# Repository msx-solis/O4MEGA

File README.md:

# o4Mega v1.
4Mb expansion for OMEGA MSX2+ HOME COMPUTER.
Here is my first board design to expand OMEGA Home Computer from 1Mb to 4Mb of static RAM.
This design is optimized to manufacture the pcb with the toner transfer technique.

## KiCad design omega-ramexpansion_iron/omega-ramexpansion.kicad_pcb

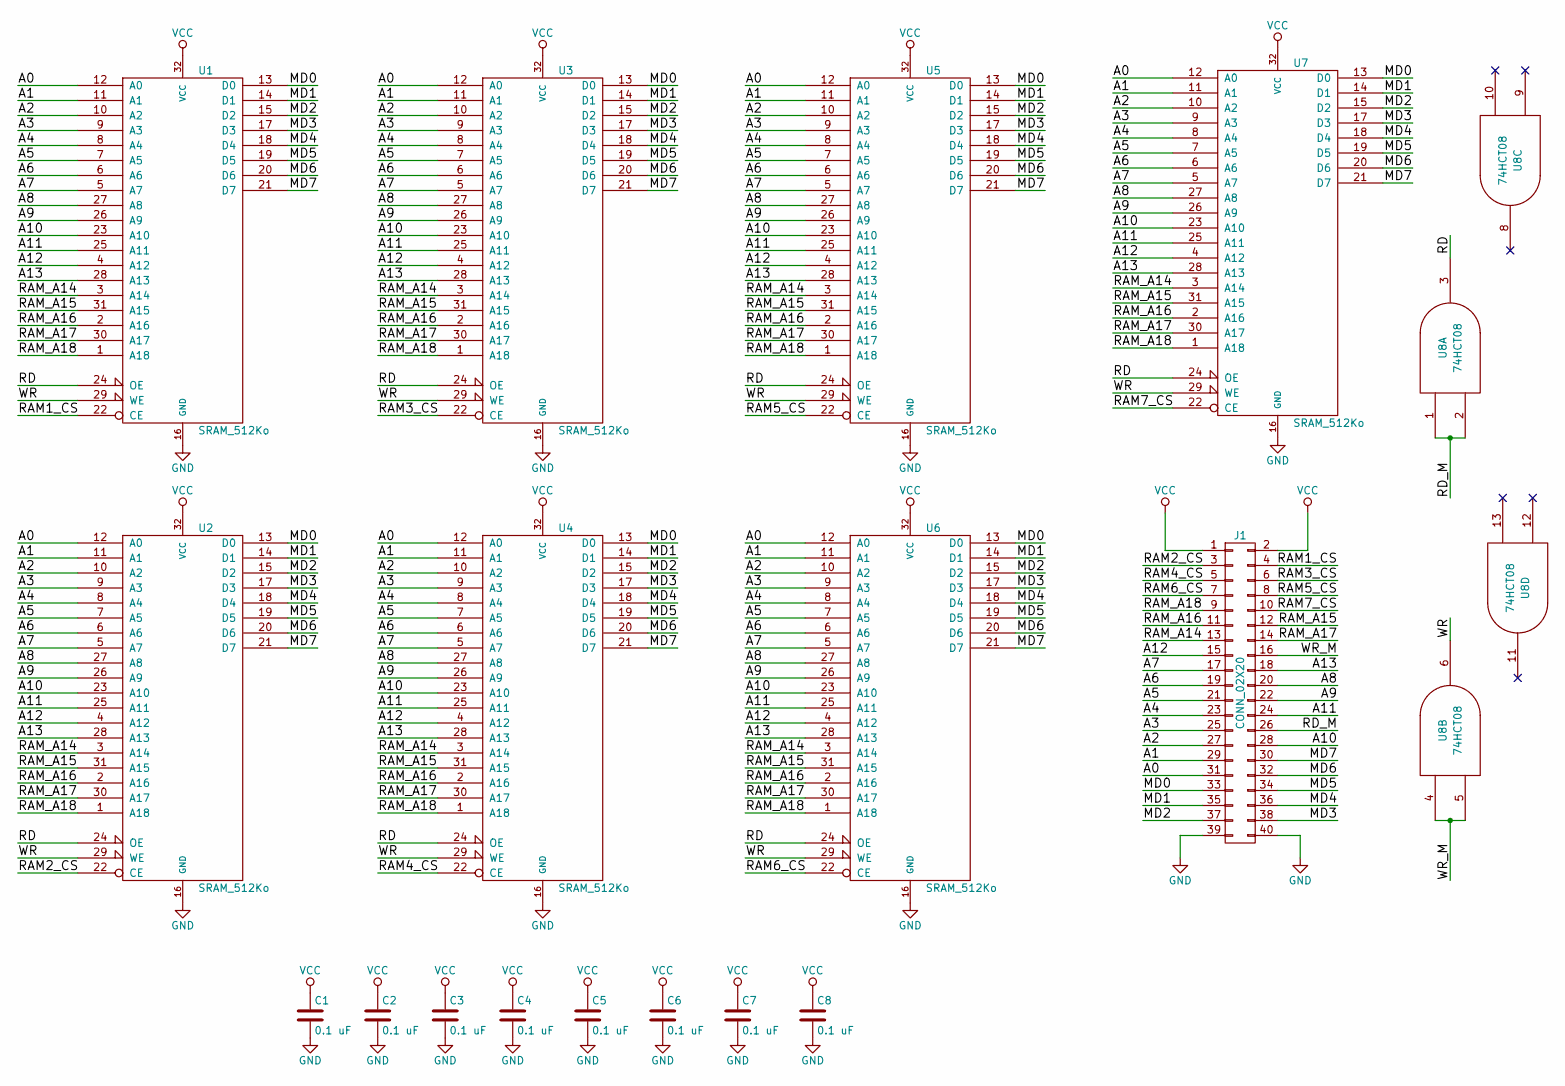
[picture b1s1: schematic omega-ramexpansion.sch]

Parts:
C1, C2, C3, C4, C5, C6, C7, C8: 0.1 uF; C_Disc_D7.5mm_W2.5mm_P5.00mm
J1: CONN_02X20; Socket_Strip_Straight_2x20_Pitch2.54mm
U1, U2, U3, U4, U5, U6, U7: SRAM_512Ko; DIP-32_W15.24mm_LongPads
U8: 74HCT08; DIP-14_W7.62mm_LongPads

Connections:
/A0: J1.31, U1.12 (A0), U2.12 (A0), U3.12 (A0), U4.12 (A0), U5.12 (A0), U6.12 (A0), U7.12 (A0)
/A1: J1.29, U1.11 (A1), U2.11 (A1), U3.11 (A1), U4.11 (A1), U5.11 (A1), U6.11 (A1), U7.11 (A1)
/A2: J1.27, U1.10 (A2), U2.10 (A2), U3.10 (A2), U4.10 (A2), U5.10 (A2), U6.10 (A2), U7.10 (A2)
/A3: J1.25, U1.9 (A3), U2.9 (A3), U3.9 (A3), U4.9 (A3), U5.9 (A3), U6.9 (A3), U7.9 (A3)
/A4: J1.23, U1.8 (A4), U2.8 (A4), U3.8 (A4), U4.8 (A4), U5.8 (A4), U6.8 (A4), U7.8 (A4)
/A5: J1.21, U1.7 (A5), U2.7 (A5), U3.7 (A5), U4.7 (A5), U5.7 (A5), U6.7 (A5), U7.7 (A5)
/A6: J1.19, U1.6 (A6), U2.6 (A6), U3.6 (A6), U4.6 (A6), U5.6 (A6), U6.6 (A6), U7.6 (A6)
/A7: J1.17, U1.5 (A7), U2.5 (A7), U3.5 (A7), U4.5 (A7), U5.5 (A7), U6.5 (A7), U7.5 (A7)
/A8: J1.20, U1.27 (A8), U2.27 (A8), U3.27 (A8), U4.27 (A8), U5.27 (A8), U6.27 (A8), U7.27 (A8)
/A9: J1.22, U1.26 (A9), U2.26 (A9), U3.26 (A9), U4.26 (A9), U5.26 (A9), U6.26 (A9), U7.26 (A9)
/A10: J1.28, U1.23 (A10), U2.23 (A10), U3.23 (A10), U4.23 (A10), U5.23 (A10), U6.23 (A10), U7.23 (A10)
/A11: J1.24, U1.25 (A11), U2.25 (A11), U3.25 (A11), U4.25 (A11), U5.25 (A11), U6.25 (A11), U7.25 (A11)
/A12: J1.15, U1.4 (A12), U2.4 (A12), U3.4 (A12), U4.4 (A12), U5.4 (A12), U6.4 (A12), U7.4 (A12)
/A13: J1.18, U1.28 (A13), U2.28 (A13), U3.28 (A13), U4.28 (A13), U5.28 (A13), U6.28 (A13), U7.28 (A13)
/MD0: J1.33, U1.13 (D0), U2.13 (D0), U3.13 (D0), U4.13 (D0), U5.13 (D0), U6.13 (D0), U7.13 (D0)
/MD1: J1.35, U1.14 (D1), U2.14 (D1), U3.14 (D1), U4.14 (D1), U5.14 (D1), U6.14 (D1), U7.14 (D1)
/MD2: J1.37, U1.15 (D2), U2.15 (D2), U3.15 (D2), U4.15 (D2), U5.15 (D2), U6.15 (D2), U7.15 (D2)
/MD3: J1.38, U1.17 (D3), U2.17 (D3), U3.17 (D3), U4.17 (D3), U5.17 (D3), U6.17 (D3), U7.17 (D3)
/MD4: J1.36, U1.18 (D4), U2.18 (D4), U3.18 (D4), U4.18 (D4), U5.18 (D4), U6.18 (D4), U7.18 (D4)
/MD5: J1.34, U1.19 (D5), U2.19 (D5), U3.19 (D5), U4.19 (D5), U5.19 (D5), U6.19 (D5), U7.19 (D5)
/MD6: J1.32, U1.20 (D6), U2.20 (D6), U3.20 (D6), U4.20 (D6), U5.20 (D6), U6.20 (D6), U7.20 (D6)
/MD7: J1.30, U1.21 (D7), U2.21 (D7), U3.21 (D7), U4.21 (D7), U5.21 (D7), U6.21 (D7), U7.21 (D7)
/RAM1_CS: J1.4, U1.22 (CE)
/RAM2_CS: J1.3, U2.22 (CE)
/RAM3_CS: J1.6, U3.22 (CE)
/RAM4_CS: J1.5, U4.22 (CE)
/RAM5_CS: J1.8, U5.22 (CE)
/RAM6_CS: J1.7, U6.22 (CE)
/RAM7_CS: J1.10, U7.22 (CE)
/RAM_A14: J1.13, U1.3 (A14), U2.3 (A14), U3.3 (A14), U4.3 (A14), U5.3 (A14), U6.3 (A14), U7.3 (A14)
/RAM_A15: J1.12, U1.31 (A15), U2.31 (A15), U3.31 (A15), U4.31 (A15), U5.31 (A15), U6.31 (A15), U7.31 (A15)
/RAM_A16: J1.11, U1.2 (A16), U2.2 (A16), U3.2 (A16), U4.2 (A16), U5.2 (A16), U6.2 (A16), U7.2 (A16)
/RAM_A17: J1.14, U1.30 (A17), U2.30 (A17), U3.30 (A17), U4.30 (A17), U5.30 (A17), U6.30 (A17), U7.30 (A17)
/RAM_A18: J1.9, U1.1 (A18), U2.1 (A18), U3.1 (A18), U4.1 (A18), U5.1 (A18), U6.1 (A18), U7.1 (A18)
/RD: U1.24 (OE), U2.24 (OE), U3.24 (OE), U4.24 (OE), U5.24 (OE), U6.24 (OE), U7.24 (OE), U8.3
/RD_M: J1.26, U8.1, U8.2
/WR: U1.29 (WE), U2.29 (WE), U3.29 (WE), U4.29 (WE), U5.29 (WE), U6.29 (WE), U7.29 (WE), U8.6
/WR_M: J1.16, U8.4, U8.5
GND: C1.2, C2.2, C3.2, C4.2, C5.2, C6.2, C7.2, C8.2, J1.39, J1.40, U1.16 (GND), U2.16 (GND), U3.16 (GND), U4.16 (GND), U5.16 (GND), U6.16 (GND), U7.16 (GND), U8.7 (GND)
VCC: C1.1, C2.1, C3.1, C4.1, C5.1, C6.1, C7.1, C8.1, J1.1, J1.2, U1.32 (VCC), U2.32 (VCC), U3.32 (VCC), U4.32 (VCC), U5.32 (VCC), U6.32 (VCC), U7.32 (VCC), U8.14 (VCC)

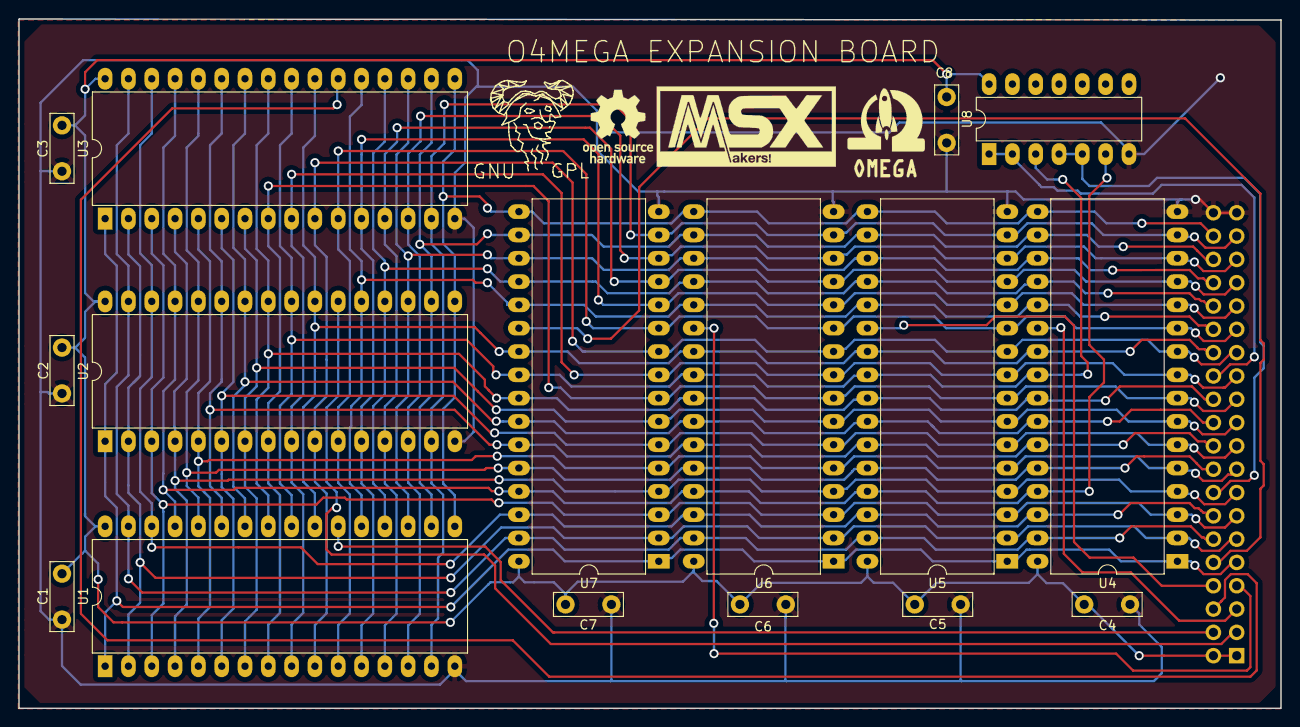
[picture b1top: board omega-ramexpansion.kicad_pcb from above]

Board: 2 copper layers, 137.5 x 75.1 mm, 17 parts (1 on the bottom side), 40 nets.
